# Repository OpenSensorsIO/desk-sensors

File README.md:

# Desk Sensor Stuff
This repo contains the Arduino code for the RFu328 ultrasonic desk sensor as well as the Node-RED flow for the hub device and the PCB EAGLE files.

Check out localhost:1880/status for output from the sensors.

https://cloud.githubusercontent.com/assets/6317446/7678626/92cf6eda-fd4d-11e4-8980-ae222dfc567b.jpg

Big acknowledgement of Oxford Flood Network, ThingInnovations and Andrew Lesley for great examples.

PS for the EAGLE files: board v3 was designed to take 6-12V input and use two Wirelessthings PowerPods (PowerPOD 1117) to transform to 3.3V (for the RFu328) and 5V (for the HC-SR04 ultrasonic device). However, it was found that these down-regulating pods have unacceptable quiescent currents. We now use board v3 with a bridge (connecting Vin to Vout for the designated 3.3V  pod), and put a PowerPOD NCP1402 to transform incoming 3.6V from a SAFT battery to 5V.

There's a board v4 with a transistor to control the quiescent draw of either ultrasonic or PIR sensors.

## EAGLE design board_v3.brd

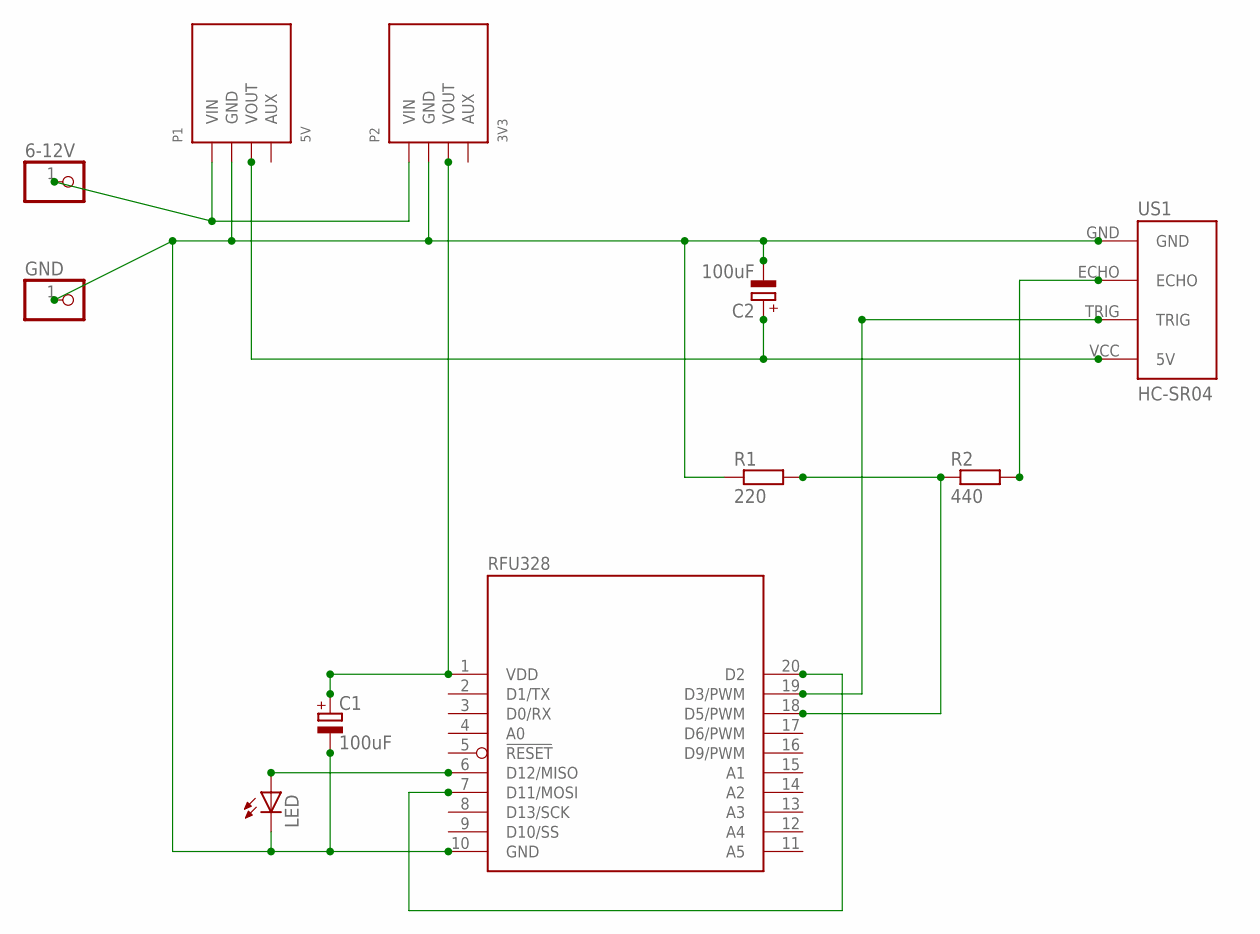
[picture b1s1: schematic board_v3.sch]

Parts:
6-12V: PINHD-1X1; 1X01
C1, C2: 100uF; E5-5
GND: PINHD-1X1; 1X01
LED: TLLR4400; LED3MM
P1: 5V; POWER-POD-REF
P2: 3V3; POWER-POD-REF
R1: 220; 0207/7
R2: 440; 0207/7
RFU328: RFµ-328-SOCKET-V2.0; RFµ-SOCKET-V2.0
US1: HC-SR04; HC-SR04_FOOTPRINT

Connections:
GND: C1.-, C2.-, GND.1, LED.K (C), P1.2 (GND), P2.2 (GND), R1.1, RFU328.10 (GND), US1.GND
unnamed: LED.A, RFU328.6 (D12/MISO)
unnamed: R2.2, US1.ECHO
unnamed: RFU328.7 (D11/MOSI), RFU328.20 (D2)
unnamed: C2.+, P1.3 (VOUT), US1.VCC (5V)
unnamed: R1.2, R2.1, RFU328.18 (D5/PWM)
unnamed: RFU328.19 (D3/PWM), US1.TRIG
unnamed: 6-12V.1, P1.1 (VIN), P2.1 (VIN)
VDD: C1.+, P2.3 (VOUT), RFU328.1 (VDD)

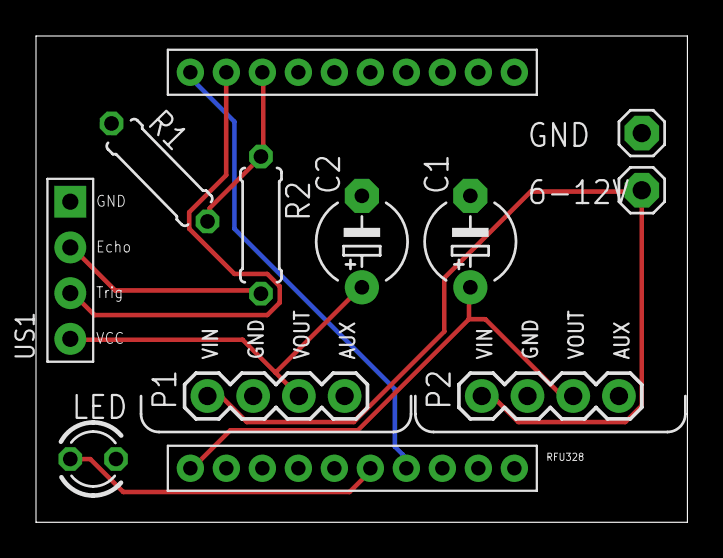
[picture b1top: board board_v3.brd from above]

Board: 2 copper layers, 36.2 x 27.0 mm, 11 parts (0 on the bottom side), 9 nets.
